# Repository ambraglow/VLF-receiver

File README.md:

# E202 VLF receiver
This is my own spin on the E202 VLF receiver design, as a PCB.
It features 2.1mm mounting holes, a line-out audio transformer (so it can be directly connected to a soundcard) and a volume control slider.  

## June update
Today on June 16th i received a batch of boards, thanks to [PCBWay](https://www.pcbway.com/) for sponsoring this project!
The ordering process is pretty straightforward, i used their Kicad plugin for exporting production files and uploading them to their system.
Compared to their conpetitors, different soldermask colors don't add too much cost to production and look stunning, shipping times aren't too bad either, it took less than a week for the PCBs to arrive to Italy, it was an overall pleasant experience and their support is also really helpful as i had to ask for help with my order at some point, because of a different revision of my board.
Here's some pictures of the boards, they really look stunning in yellow soldermask.

Functionally they should work, but that will be a problem for future me :D  

## Credits & Resources
[Original schematic design](http://www.vlf.it/romero2/explorer-e202.html) by Renato | [rendered PCB images, thanks to Lina's plugin](https://github.com/linalinn/kicad-render)

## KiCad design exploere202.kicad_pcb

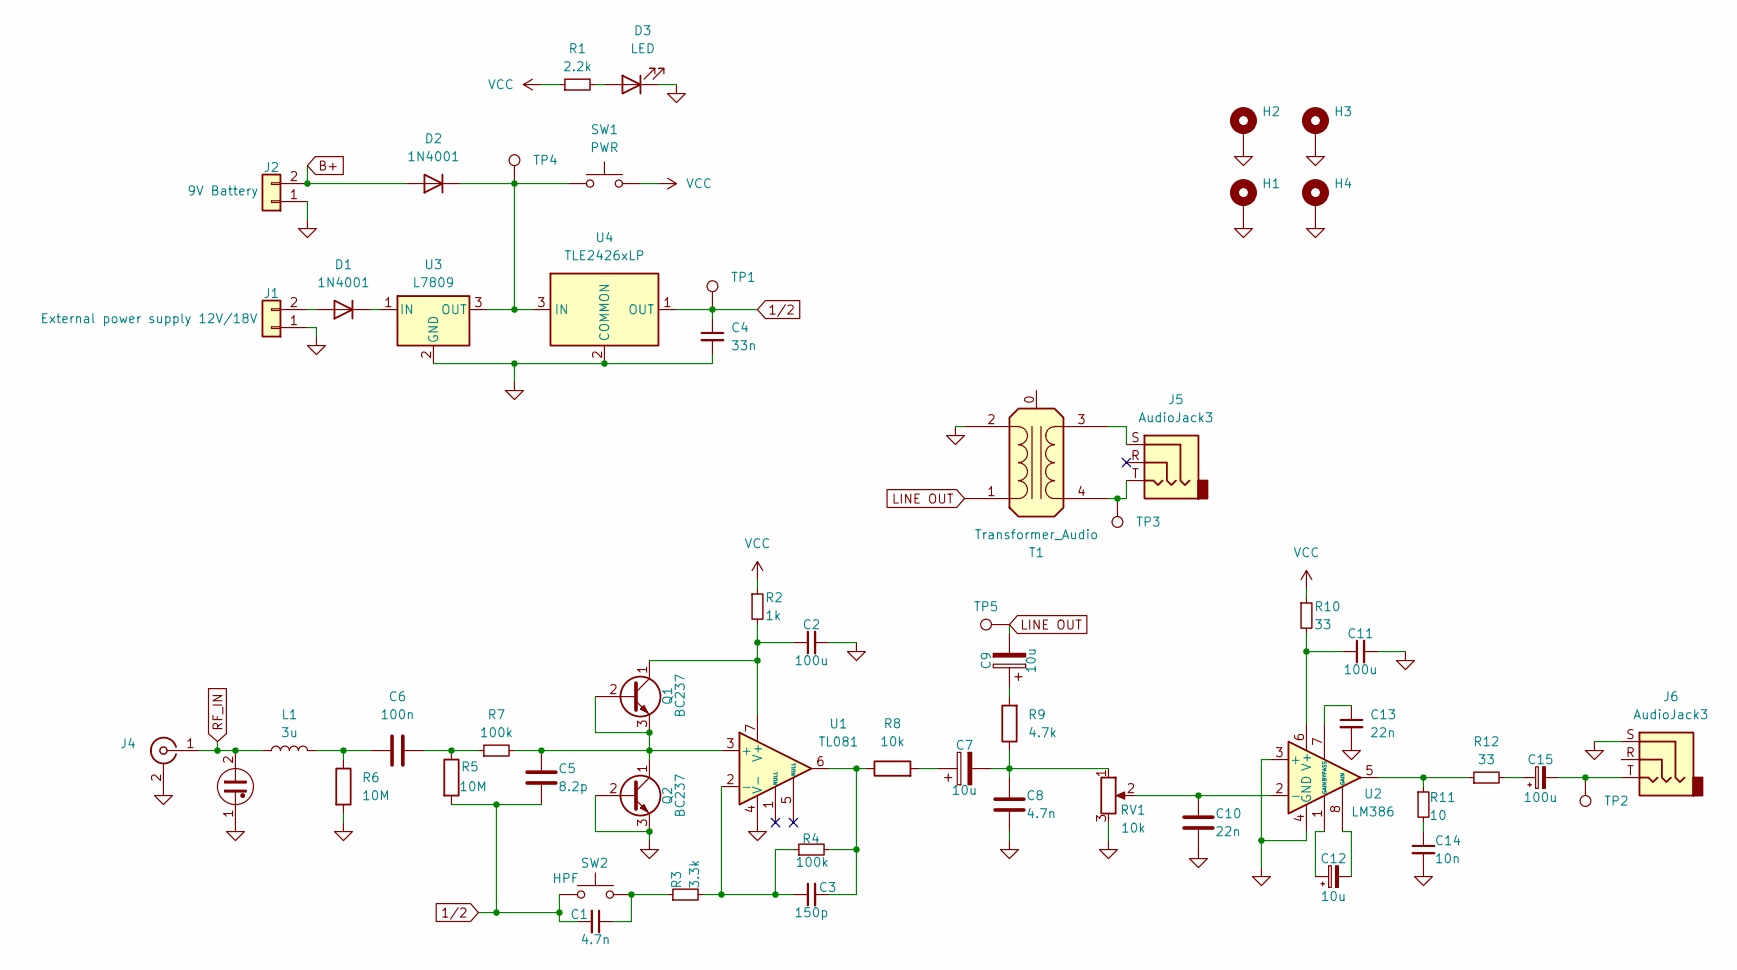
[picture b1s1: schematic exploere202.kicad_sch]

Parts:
C1, C8: 4.7n; C_0603_1608Metric
C2, C11: 100u; C_0805_2012Metric
C3: 150p; C_0603_1608Metric
C4: 33n; C_0603_1608Metric
C5: 8.2p; C_0603_1608Metric
C6: 100n; C_0603_1608Metric
C7, C9, C12: 10u; CP_Elec_6.3x4.5
C10, C13: 22n; C_0603_1608Metric
C14: 10n; C_0603_1608Metric
C15: 100u; CP_Radial_D6.3mm_P2.50mm
D1, D2: 1N4001; D_SOD-123
D3: LED; LED_0603_1608Metric
H1, H2, H3, H4: MountingHole_Pad; MountingHole_2.1mm
J1: External power supply 12V/18V; PinHeader_1x02_P2.54mm_Vertical
J2: 9V Battery; PinHeader_1x02_P2.54mm_Vertical
J4: Conn_Coaxial; BNC_Win_364A2x95_Horizontal
J5, J6: AudioJack3; Jack_3.5mm_CUI_SJ-3523-SMT_Horizontal
L1: 3u; L_0603_1608Metric
NE1: Lamp_Neon; Valve_Glimm
Q1, Q2: BC237; SOT-23-3
R1: 2.2k; R_0402_1005Metric
R2: 1k; R_0603_1608Metric
R3: 3.3k; R_0603_1608Metric
R4, R7: 100k; R_0603_1608Metric
R5, R6: 10M; R_0603_1608Metric
R8: 10k; R_0603_1608Metric
R9: 4.7k; R_0603_1608Metric
R10, R12: 33; R_0603_1608Metric
R11: 10; R_0603_1608Metric
RV1: 10k; RES-ADJ-TH_RS30111A602N
SW1: PWR; SW-TH_ST-0-102-C03-N003-RS
SW2: HPF; SW-TH_ST-0-102-C03-N003-RS
T1: Transformer_Audio; Transformer_ED8_4-Lead_10.5x8mm_P5mm
TP1, TP2, TP4, TP5: TestPoint; TestPoint_Pad_D2.5mm
TP3: TestPoint; TestPoint_Pad_D1.5mm
U1: TL081; SOIC-8-1EP_3.9x4.9mm_P1.27mm_EP2.29x3mm
U2: LM386; SOIC-8-1EP_3.9x4.9mm_P1.27mm_EP2.29x3mm
U3: L7809; TO-263-3_TabPin2
U4: TLE2426xLP; SOIC-8-1EP_3.9x4.9mm_P1.27mm_EP2.29x3mm

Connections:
1/2: C1.2, C4.1, C5.2, R5.2, SW2.2, TP1.1, U4.1 (OUT)
B+: D2.2 (A), J2.2
GND: C2.2, C4.2, C8.2, C10.2, C11.2, C13.2, C14.2, D3.1 (K), H1.1, H2.1, H3.1, H4.1, J1.1, J2.1, J4.2 (Ext), J6.S, NE1.1, Q2.2 (B), Q2.3 (E), R6.2, RV1.3, T1.2 (AB), U1.4 (V-), U2.3 (+), U2.4 (GND), U3.2 (GND), U4.2 (COMMON)
LINE OUT: C9.2, T1.1 (AA), TP5.1
unnamed: C1.1, R3.1, SW2.1
unnamed: C3.2, R4.2, R8.1, U1.6
unnamed: C6.1, L1.2, R6.1
unnamed: C6.2, R5.1, R7.1
unnamed: C7.1, R8.2
unnamed: C7.2, C8.1, R9.1, RV1.1
unnamed: C9.1, R9.2
unnamed: C12.1, U2.1 (GAIN)
unnamed: C12.2, U2.8 (GAIN)
unnamed: C14.1, R11.2
unnamed: C15.1, R12.2
unnamed: C15.2, J6.T, TP2.1
unnamed: D1.2 (A), J1.2
unnamed: D1.1 (K), U3.1 (IN)
unnamed: D2.1 (K), SW1.1, TP4.1, U3.3 (OUT), U4.3 (IN)
unnamed: D3.2 (A), R1.2
unnamed: C5.1, Q1.2 (B), Q1.3 (E), Q2.1 (C), R7.2, U1.3 (+)
unnamed: C2.1, Q1.1 (C), R2.2, U1.7 (V+)
unnamed: R11.1, R12.1, U2.5
unnamed: J5.S, T1.3 (SA)
unnamed: J5.T, T1.4 (SB), TP3.1
unnamed: C3.1, R3.2, R4.1, U1.2 (-)
unnamed: C10.1, RV1.2, U2.2 (-)
unnamed: C13.1, U2.7 (BYPASS)
unnamed: C11.1, R10.2, U2.6 (V+)
RF_IN: J4.1 (In), L1.1, NE1.2
VCC: R1.1, R2.1, R10.1, SW1.2

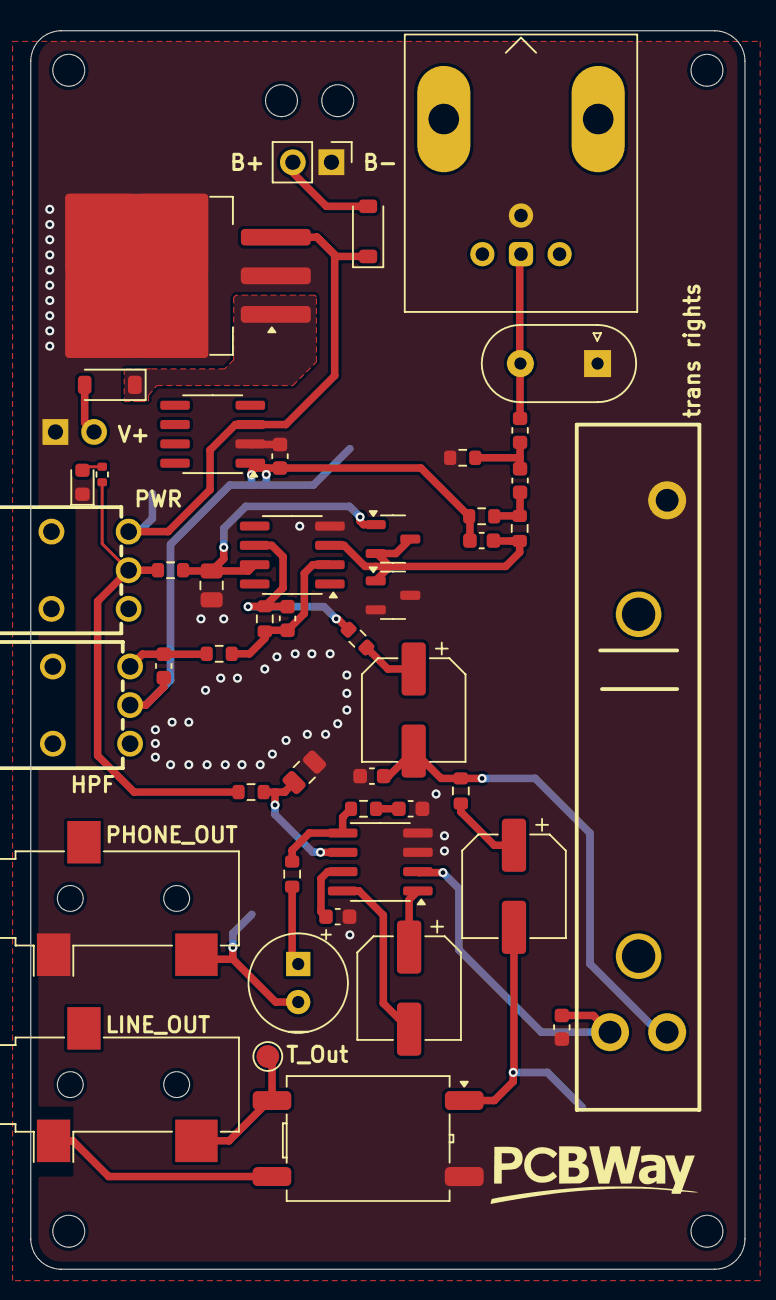
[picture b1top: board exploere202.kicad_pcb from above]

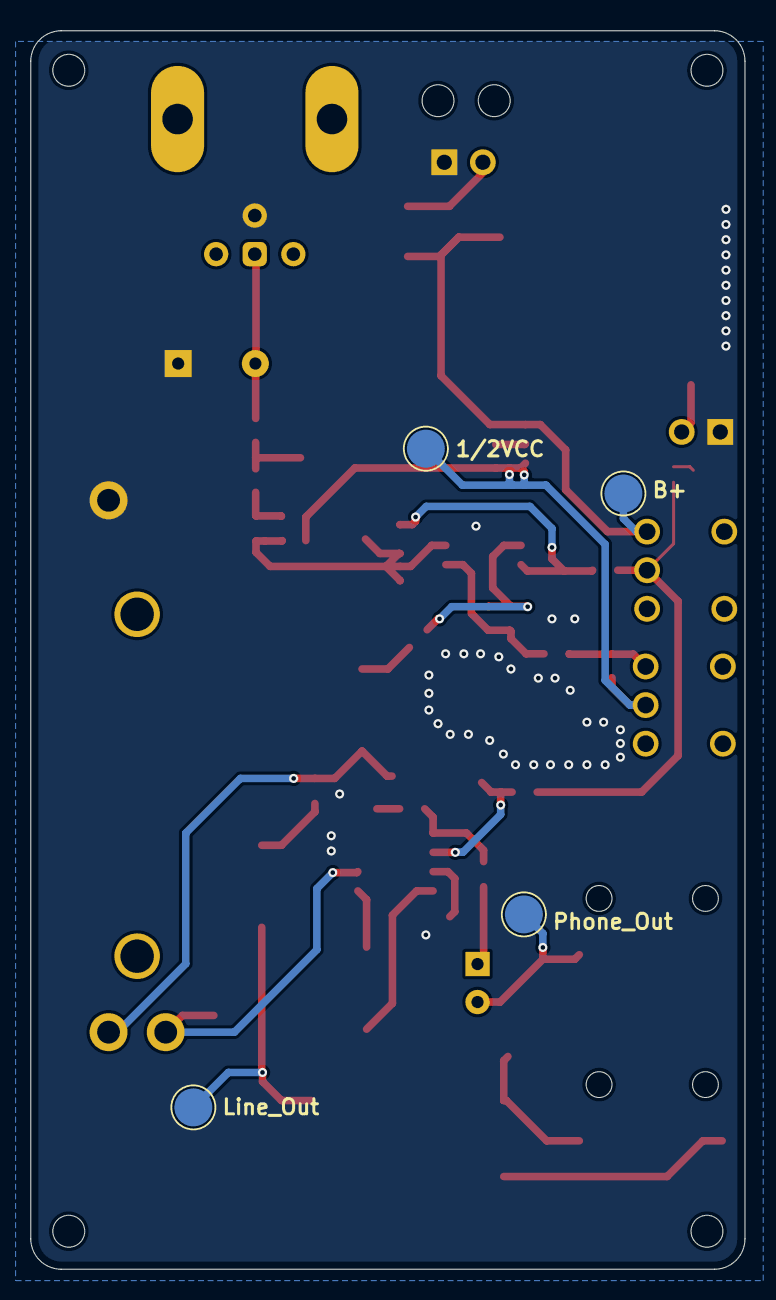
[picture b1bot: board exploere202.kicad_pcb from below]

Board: 2 copper layers, 47.0 x 81.5 mm, 56 parts (4 on the bottom side), 31 nets.

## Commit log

2025-06-02 Update LICENSE
2025-06-16 add board images!
2025-06-16 board images in folder
2025-09-08 Update README.md
    collect my pages
